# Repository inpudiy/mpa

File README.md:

# MPA

MPA is a 42-key split keyboard built on the CHOC V1 platform using Chocfox spacing.

[Build Guide](https://github.com/inpudiy/mpa/blob/main/build_guide.md) - [ZMK Firmware](https://github.com/inpudiy/mpa_zmk-config/releases)

## Features

- Supports Chocfox spacing (17.5 × 17.5 mm)  
- Optimized for wireless: hardware power switch, reset button, battery solder pads, no LEDs, and ZMK firmware  
- 42-key layout with an aggressive column-stagger inspired by the Jian keyboard  
- CHOC V1 switches only  
- Pro Micro format microcontroller Compatible with hot-swap installation  
- 3D-printed case  

---

## Bill of Materials (BOM)

| Component                                                    | Qty |
| ------------------------------------------------------------ | --- |
| Microcontroller: nRFMicro / Super Mini nRF52840 / nice!nano  | 2   |
| Power switch: SUNGMUN BSI-10H                                | 2   |
| 301230 battery                                               | 2   |
| Turtle Switch SMD 2-pin (3 × 4 × 2 mm)                        | 2   |
| Silicone bumpers (6 × 2 mm)                                  | 4   |
| Pin Header Female 13 pin (2.54mm)                             | 4   | 
| Plastic heat-set insert nut M2 (OD 3.2 mm, length 3 mm)      | 14  |
| Countersunk head screw M2 (length 4 mm)                      | 14  |
| PG1350 hot-swap socket                                       | 42  |
| Diode 1N4148W (SOD-323)                                      | 42  |
| CHOC V1 switches                                             | 42  |
| Chocfox 1U keycaps                                           | 42  |

## PCB Image

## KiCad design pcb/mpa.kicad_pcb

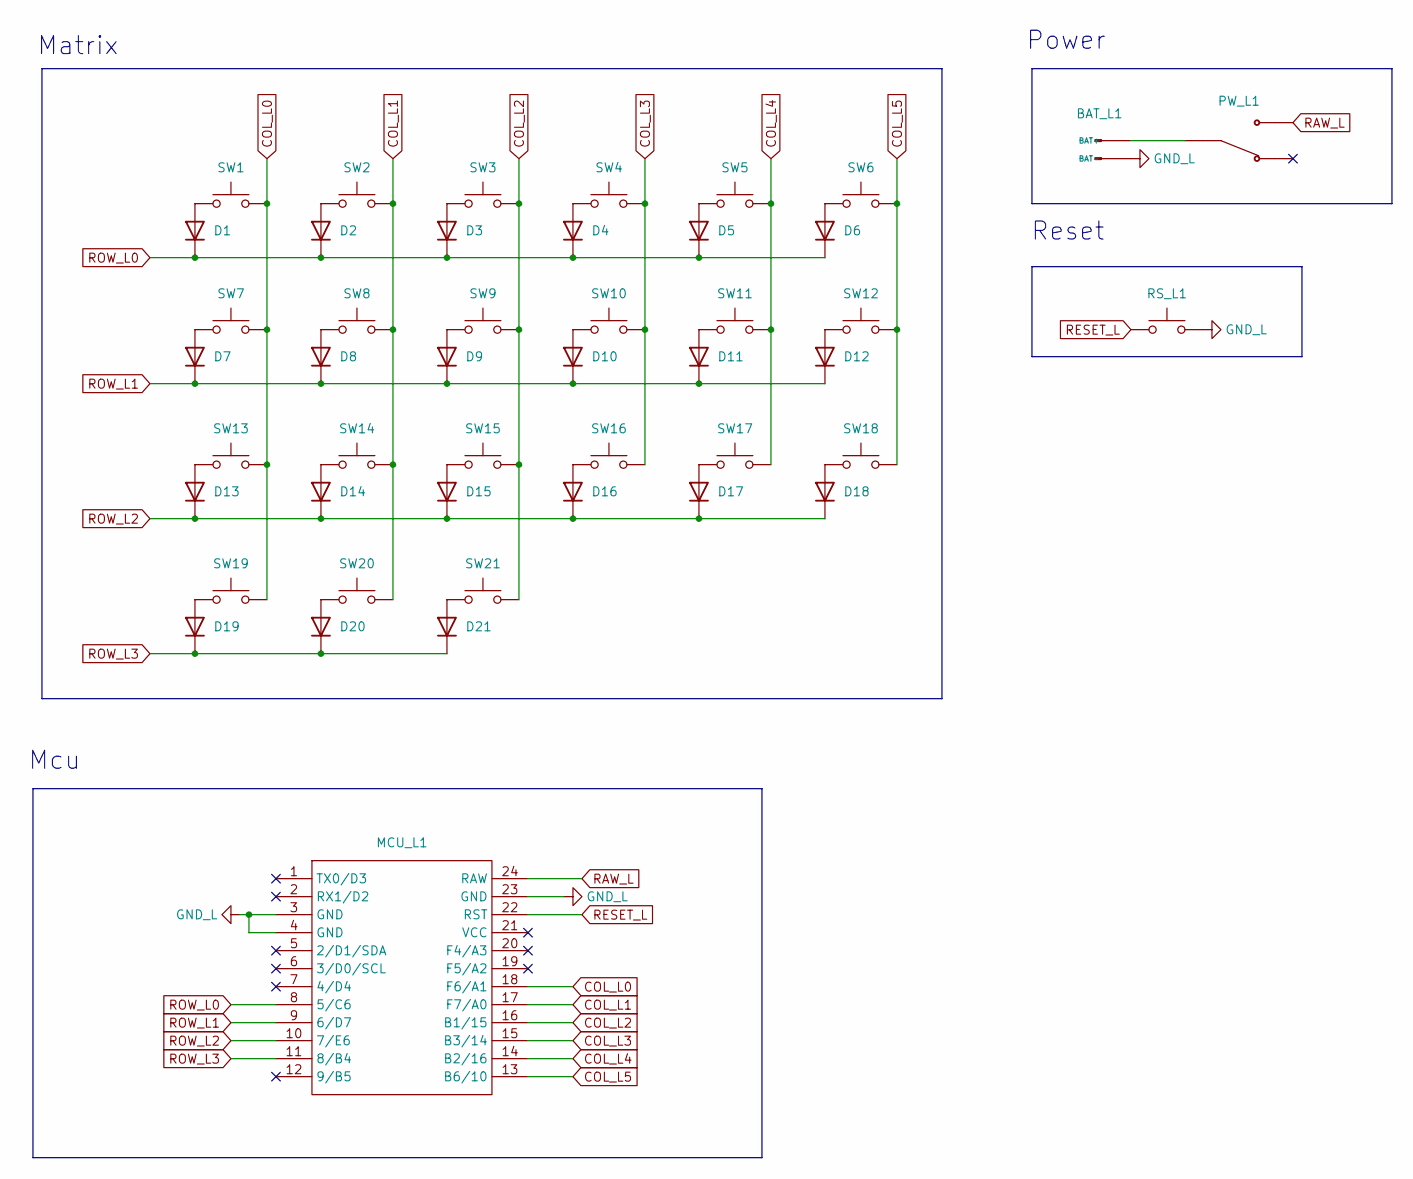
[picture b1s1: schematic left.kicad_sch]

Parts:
BAT_L1: Battery
D1, D2, D3, D4, D5, D6, D7, D8, D9, D10, D11, D12, D13, D14, D15, D16, D17, D18, D19, D20, D21: Diode; SOD323
MCU_L1: ProMicro_NN
PW_L1: BSI-10H
RS_L1: Reset
SW1, SW2, SW3, SW4, SW5, SW6, SW7, SW8, SW9, SW10, SW11, SW12, SW13, SW14, SW15, SW16, SW17, SW18, SW19, SW20, SW21: Kailh PG1350

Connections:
COL_L0: MCU_L1.18 (F6/A1), SW1.2, SW7.2, SW13.2, SW19.2
COL_L1: MCU_L1.17 (F7/A0), SW2.2, SW8.2, SW14.2, SW20.2
COL_L2: MCU_L1.16 (B1/15), SW3.2, SW9.2, SW15.2, SW21.2
COL_L3: MCU_L1.15 (B3/14), SW4.2, SW10.2, SW16.2
COL_L4: MCU_L1.14 (B2/16), SW5.2, SW11.2, SW17.2
COL_L5: MCU_L1.13 (B6/10), SW6.2, SW12.2, SW18.2
GND_L: BAT_L1.2 (BAT-), MCU_L1.3 (GND), MCU_L1.4 (GND), MCU_L1.23 (GND), RS_L1.2
unnamed: BAT_L1.1 (BAT+), PW_L1.1
unnamed: D1.2 (A), SW1.1
unnamed: D2.2 (A), SW2.1
unnamed: D3.2 (A), SW3.1
unnamed: D4.2 (A), SW4.1
unnamed: D5.2 (A), SW5.1
unnamed: D6.2 (A), SW6.1
unnamed: D7.2 (A), SW7.1
unnamed: D8.2 (A), SW8.1
unnamed: D9.2 (A), SW9.1
unnamed: D10.2 (A), SW10.1
unnamed: D11.2 (A), SW11.1
unnamed: D12.2 (A), SW12.1
unnamed: D13.2 (A), SW13.1
unnamed: D14.2 (A), SW14.1
unnamed: D15.2 (A), SW15.1
unnamed: D16.2 (A), SW16.1
unnamed: D17.2 (A), SW17.1
unnamed: D18.2 (A), SW18.1
unnamed: D19.2 (A), SW19.1
unnamed: D20.2 (A), SW20.1
unnamed: D21.2 (A), SW21.1
RAW_L: MCU_L1.24 (RAW), PW_L1.2
RESET_L: MCU_L1.22 (RST), RS_L1.1
ROW_L0: D1.1 (K), D2.1 (K), D3.1 (K), D4.1 (K), D5.1 (K), D6.1 (K), MCU_L1.8 (5/C6)
ROW_L1: D7.1 (K), D8.1 (K), D9.1 (K), D10.1 (K), D11.1 (K), D12.1 (K), MCU_L1.9 (6/D7)
ROW_L2: D13.1 (K), D14.1 (K), D15.1 (K), D16.1 (K), D17.1 (K), D18.1 (K), MCU_L1.10 (7/E6)
ROW_L3: D19.1 (K), D20.1 (K), D21.1 (K), MCU_L1.11 (8/B4)

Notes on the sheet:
Power
Matrix
Reset
Mcu

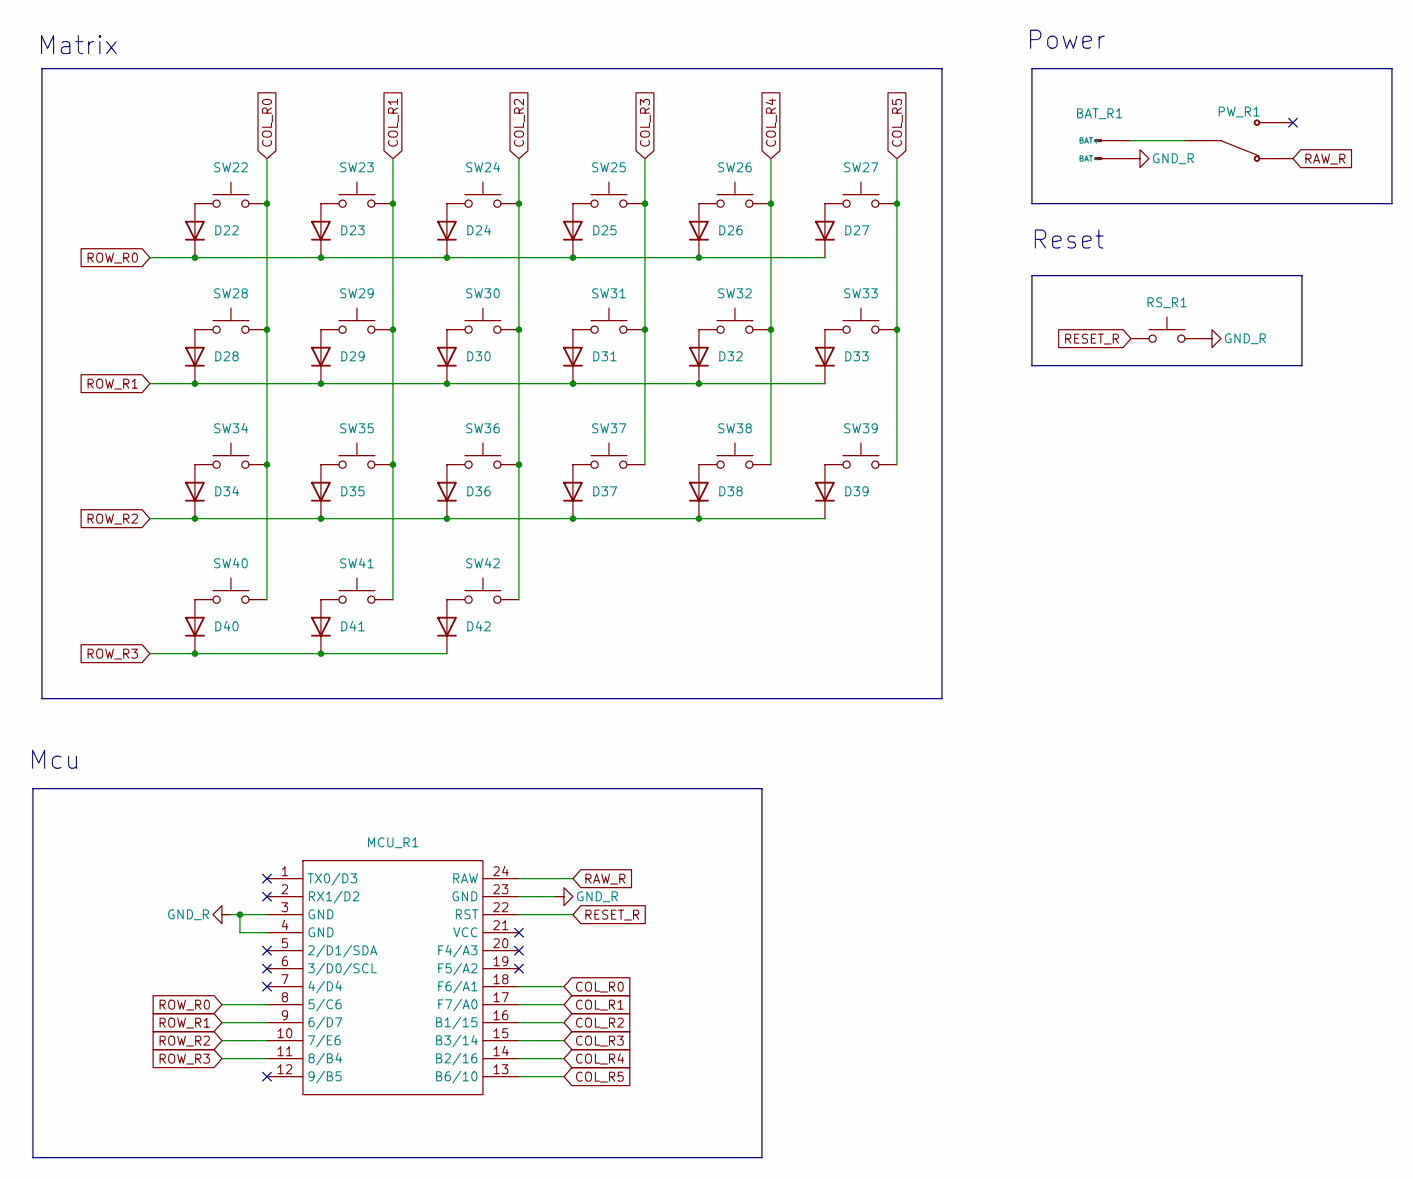
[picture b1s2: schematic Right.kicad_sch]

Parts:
BAT_R1: Battery
D22, D23, D24, D25, D26, D27, D28, D29, D30, D31, D32, D33, D34, D35, D36, D37, D38, D39, D40, D41, D42: Diode; SOD323
MCU_R1: ProMicro_NN
PW_R1: BSI-10H
RS_R1: Reset
SW22, SW23, SW24, SW25, SW26, SW27, SW28, SW29, SW30, SW31, SW32, SW33, SW34, SW35, SW36, SW37, SW38, SW39, SW40, SW41, SW42: Kailh PG1350

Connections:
COL_R0: MCU_R1.18 (F6/A1), SW22.2, SW28.2, SW34.2, SW40.2
COL_R1: MCU_R1.17 (F7/A0), SW23.2, SW29.2, SW35.2, SW41.2
COL_R2: MCU_R1.16 (B1/15), SW24.2, SW30.2, SW36.2, SW42.2
COL_R3: MCU_R1.15 (B3/14), SW25.2, SW31.2, SW37.2
COL_R4: MCU_R1.14 (B2/16), SW26.2, SW32.2, SW38.2
COL_R5: MCU_R1.13 (B6/10), SW27.2, SW33.2, SW39.2
GND_R: BAT_R1.2 (BAT-), MCU_R1.3 (GND), MCU_R1.4 (GND), MCU_R1.23 (GND), RS_R1.2
unnamed: BAT_R1.1 (BAT+), PW_R1.1
unnamed: D22.2 (A), SW22.1
unnamed: D23.2 (A), SW23.1
unnamed: D24.2 (A), SW24.1
unnamed: D25.2 (A), SW25.1
unnamed: D26.2 (A), SW26.1
unnamed: D27.2 (A), SW27.1
unnamed: D28.2 (A), SW28.1
unnamed: D29.2 (A), SW29.1
unnamed: D30.2 (A), SW30.1
unnamed: D31.2 (A), SW31.1
unnamed: D32.2 (A), SW32.1
unnamed: D33.2 (A), SW33.1
unnamed: D34.2 (A), SW34.1
unnamed: D35.2 (A), SW35.1
unnamed: D36.2 (A), SW36.1
unnamed: D37.2 (A), SW37.1
unnamed: D38.2 (A), SW38.1
unnamed: D39.2 (A), SW39.1
unnamed: D40.2 (A), SW40.1
unnamed: D41.2 (A), SW41.1
unnamed: D42.2 (A), SW42.1
RAW_R: MCU_R1.24 (RAW), PW_R1.3
RESET_R: MCU_R1.22 (RST), RS_R1.1
ROW_R0: D22.1 (K), D23.1 (K), D24.1 (K), D25.1 (K), D26.1 (K), D27.1 (K), MCU_R1.8 (5/C6)
ROW_R1: D28.1 (K), D29.1 (K), D30.1 (K), D31.1 (K), D32.1 (K), D33.1 (K), MCU_R1.9 (6/D7)
ROW_R2: D34.1 (K), D35.1 (K), D36.1 (K), D37.1 (K), D38.1 (K), D39.1 (K), MCU_R1.10 (7/E6)
ROW_R3: D40.1 (K), D41.1 (K), D42.1 (K), MCU_R1.11 (8/B4)

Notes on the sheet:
Mcu
Power
Reset
Matrix

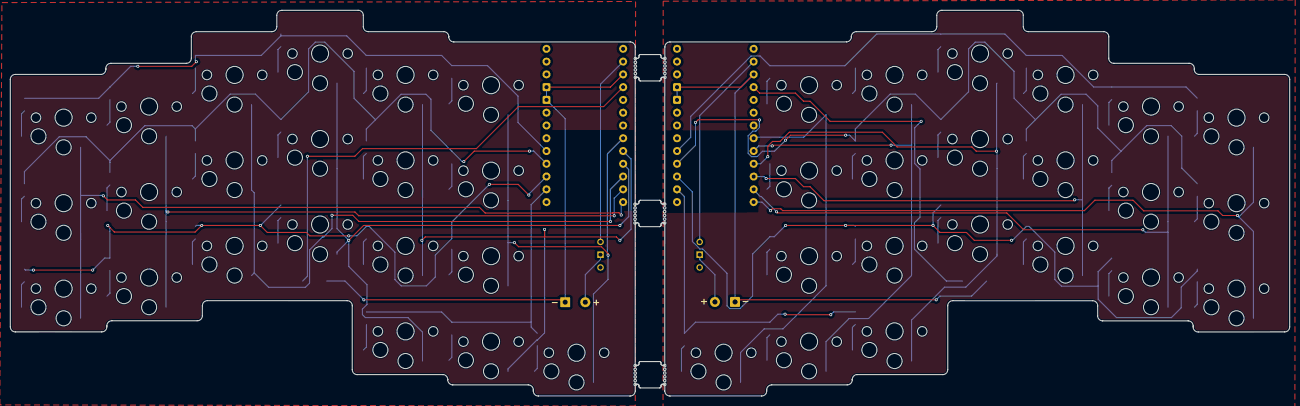
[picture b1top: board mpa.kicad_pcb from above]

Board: 2 copper layers, 254.4 x 76.7 mm, 98 parts (0 on the bottom side), 70 nets.

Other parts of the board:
Hole: Hole
Hole#2, Hole#3, Hole#4, Hole#5, Hole#6: Hole

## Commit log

2025-05-07 upload
2025-05-07 add images
2025-05-09 upload build_guide.md
2025-05-09 add links
